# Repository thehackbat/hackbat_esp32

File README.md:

# HACKBAT ESP32 

New version of the Hackbat tool, this time based on the ESP32 C6. 

> NOTE: This version is still under test, so minor changes can be applied.

## The CPU

The new version of hackbat features a powerful [ESP32C6](https://www.espressif.com/en/products/socs/esp32-c6) from [Espressif](https://www.espressif.com). This microcontroller features a dual core RISC-V processor, WIFI6, BT LE and a bunch of peripherals. 

The package used is the WROOM-1, but it is also compatible with the 1U model adding an external antenna.

## RF

Like the original, the Hackbat ESP32 features an RF tranceiver, the [CC1101](https://www.ti.com/product/es-mx/CC1101) from Texas Instruments. 

The CC1101 is a low-cost sub-1 GHz transceiver designed for very low-power wireless applications. The circuit is mainly intended for the ISM (Industrial, Scientific and Medical) and SRD (Short Range Device) frequency bands at 315, 433, 868, and 915 MHz, but can easily be programmed for operation at other frequencies in the 300-348 MHz, 387-464 MHz and 779-928 MHz bands

The Hackbat ESP32 board includes an antenna, but can be also populate the J2 connector in order to add an SMA antenna.

## OLED

A monochrome OLED is added as an interface. The driver used in the ESP-IDF IDE is able to work with the SH1106, and ssd1306

## SDCard

The SD Card in this version uses the SDIO interface with the microcontroller, so the speed is increased with respect the first version of the board.

## Layout

The layout of the board is 2-layer with components in both layers.

## Get yours

This project is open-source so you can build your own Hackbat by sending the production files to [JLCPCB](https://jlcpcb.com/?from=controlpath).

[JLCPCB](https://jlcpcb.com/?from=controlpath) not only will manufacture your PCB, but they can also asembly your board. To do that, you have to use the BOM and the Centroid files provided in the [`production_files`](./kicad/production_files/) folder.

Remember to change the Surface Finish to LeadFree HASL to make your board ROHS compliant. Also, the original board uses a Black PCB color, so if you want to keep your Hackbat like the original, you can select this color to be sure that the silkscreen is seen correctly.

In a few days, you will receive your board at home.

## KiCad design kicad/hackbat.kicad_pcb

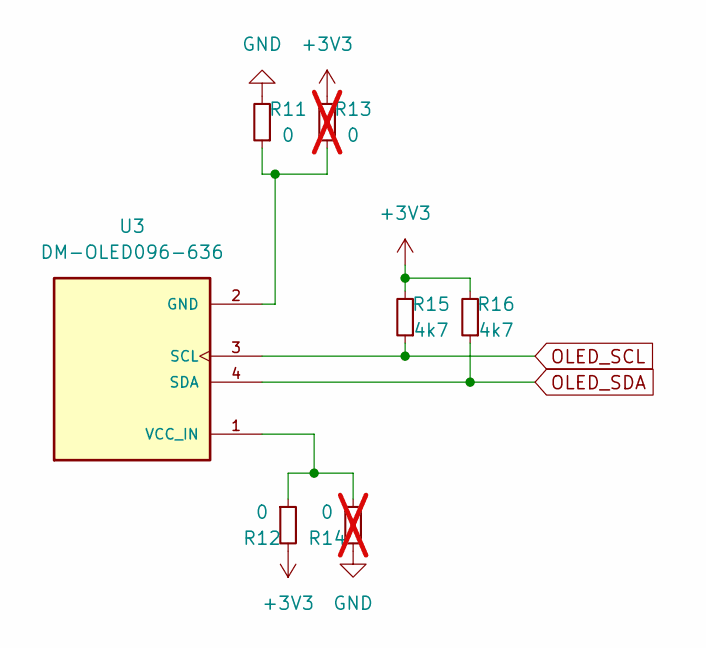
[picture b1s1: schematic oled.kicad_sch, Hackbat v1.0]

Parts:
R11, R12: 0; R_0603_1608Metric
R13, R14: 0; R_0603_1608Metric; not fitted
R15, R16: 4k7; R_0603_1608Metric
U3: DM-OLED096-636; oled_1.3; PARTREV 2018-09-10

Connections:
+3V3: R12.2, R13.2, R15.2, R16.2; also elsewhere on the board
GND: R11.2, R14.2; also elsewhere on the board
unnamed: R11.1, R13.1, U3.2 (GND)
unnamed: R12.1, R14.1, U3.1 (VCC_IN)
OLED_SCL: R15.1, U3.3 (SCL); also elsewhere on the board
OLED_SDA: R16.1, U3.4 (SDA); also elsewhere on the board

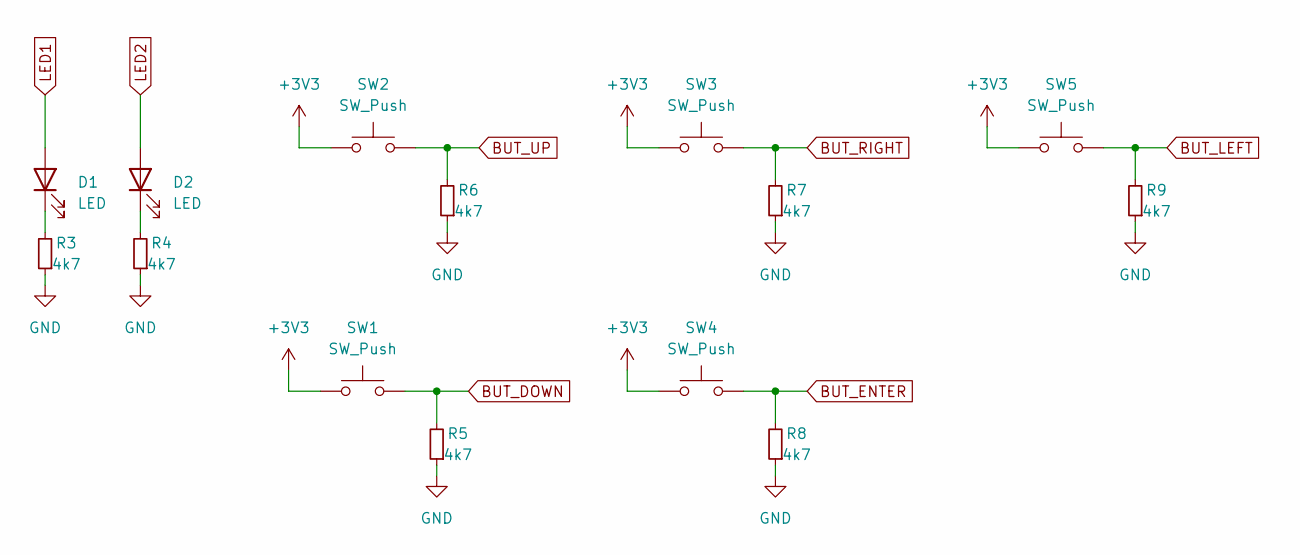
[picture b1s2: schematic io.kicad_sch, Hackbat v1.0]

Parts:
D1, D2: LED; LED_0603_1608Metric
R3, R4, R5, R6, R7, R8, R9: 4k7; R_0603_1608Metric
SW1, SW2, SW3, SW4, SW5: SW_Push; SW_Push_1P1T_NO_6x6mm_H9.5mm; JLCPCB Part # C455109

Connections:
+3V3: SW1.1, SW2.1, SW3.1, SW4.1, SW5.1; also elsewhere on the board
BUT_DOWN: R5.2, SW1.2; also elsewhere on the board
BUT_ENTER: R8.2, SW4.2; also elsewhere on the board
BUT_LEFT: R9.2, SW5.2; also elsewhere on the board
BUT_RIGHT: R7.2, SW3.2; also elsewhere on the board
BUT_UP: R6.2, SW2.2; also elsewhere on the board
GND: R3.1, R4.1, R5.1, R6.1, R7.1, R8.1, R9.1; also elsewhere on the board
LED1: D1.2 (A); also elsewhere on the board
LED2: D2.2 (A); also elsewhere on the board
unnamed: D1.1 (K), R3.2
unnamed: D2.1 (K), R4.2

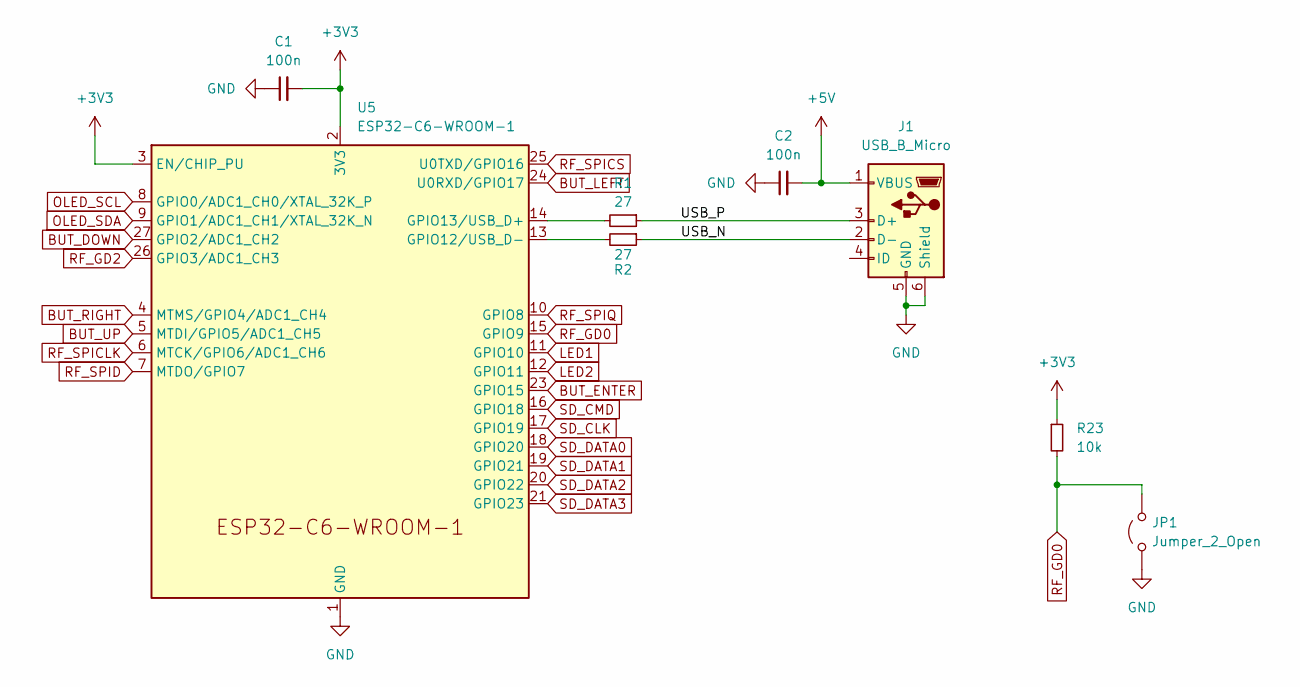
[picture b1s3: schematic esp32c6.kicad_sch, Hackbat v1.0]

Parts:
C1, C2: 100n; C_0603_1608Metric
J1: USB_B_Micro; USB_Micro-B_Amphenol_10118193-0001LF_Horizontal
JP1: Jumper_2_Open; TestPoint_2Pads_Pitch2.54mm_Drill0.8mm
R1, R2: 27; R_0603_1608Metric
R23: 10k; R_0402_1005Metric
U5: ESP32-C6-WROOM-1

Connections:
+3V3: C1.2, R23.1, U5.2 (3V3), U5.3 (EN/CHIP_PU); also elsewhere on the board
+5V: C2.2, J1.1 (VBUS); also elsewhere on the board
/esp32c6/USB_N: J1.2 (D-), R2.1
/esp32c6/USB_P: J1.3 (D+), R1.1
BUT_DOWN: U5.27 (GPIO2/ADC1_CH2); also elsewhere on the board
BUT_ENTER: U5.23 (GPIO15); also elsewhere on the board
BUT_LEFT: U5.24 (U0RXD/GPIO17); also elsewhere on the board
BUT_RIGHT: U5.4 (MTMS/GPIO4/ADC1_CH4); also elsewhere on the board
BUT_UP: U5.5 (MTDI/GPIO5/ADC1_CH5); also elsewhere on the board
GND: C1.1, C2.1, J1.5 (GND), J1.6 (Shield), JP1.1 (A), U5.1 (GND), U5.28 (GND), U5.29 (GND); also elsewhere on the board
LED1: U5.11 (GPIO10); also elsewhere on the board
LED2: U5.12 (GPIO11); also elsewhere on the board
unnamed: R2.2, U5.13 (GPIO12/USB_D-)
unnamed: R1.2, U5.14 (GPIO13/USB_D+)
OLED_SCL: U5.8 (GPIO0/ADC1_CH0/XTAL_32K_P); also elsewhere on the board
OLED_SDA: U5.9 (GPIO1/ADC1_CH1/XTAL_32K_N); also elsewhere on the board
RF_GD0: JP1.2 (B), R23.2, U5.15 (GPIO9); also elsewhere on the board
RF_GD2: U5.26 (GPIO3/ADC1_CH3); also elsewhere on the board
RF_SPICLK: U5.6 (MTCK/GPIO6/ADC1_CH6); also elsewhere on the board
RF_SPICS: U5.25 (U0TXD/GPIO16); also elsewhere on the board
RF_SPID: U5.7 (MTDO/GPIO7); also elsewhere on the board
RF_SPIQ: U5.10 (GPIO8); also elsewhere on the board
SD_CLK: U5.17 (GPIO19); also elsewhere on the board
SD_CMD: U5.16 (GPIO18); also elsewhere on the board
SD_DATA0: U5.18 (GPIO20); also elsewhere on the board
SD_DATA1: U5.19 (GPIO21); also elsewhere on the board
SD_DATA2: U5.20 (GPIO22); also elsewhere on the board
SD_DATA3: U5.21 (GPIO23); also elsewhere on the board

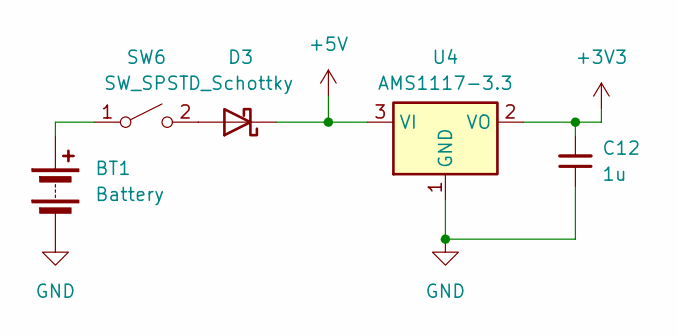
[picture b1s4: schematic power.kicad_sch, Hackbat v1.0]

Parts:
BT1: Battery; BatteryHolder_Keystone_2479_3xAAA
C12: 1u; C_0603_1608Metric
D3: D_Schottky; Nexperia_CFP3_SOD-123W; JLCPCB Part # C82544
SW6: SW_SPST; SW_SPDT_CK_JS102011SAQN; JLCPCB Part # C92658
U4: AMS1117-3.3; SOT-223-3_TabPin2

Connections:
+3V3: C12.2, U4.2 (VO); also elsewhere on the board
+5V: D3.1 (K), U4.3 (VI); also elsewhere on the board
GND: BT1.2 (-), C12.1, U4.1 (GND); also elsewhere on the board
unnamed: BT1.1 (+), SW6.1 (A)
unnamed: D3.2 (A), SW6.2 (B)

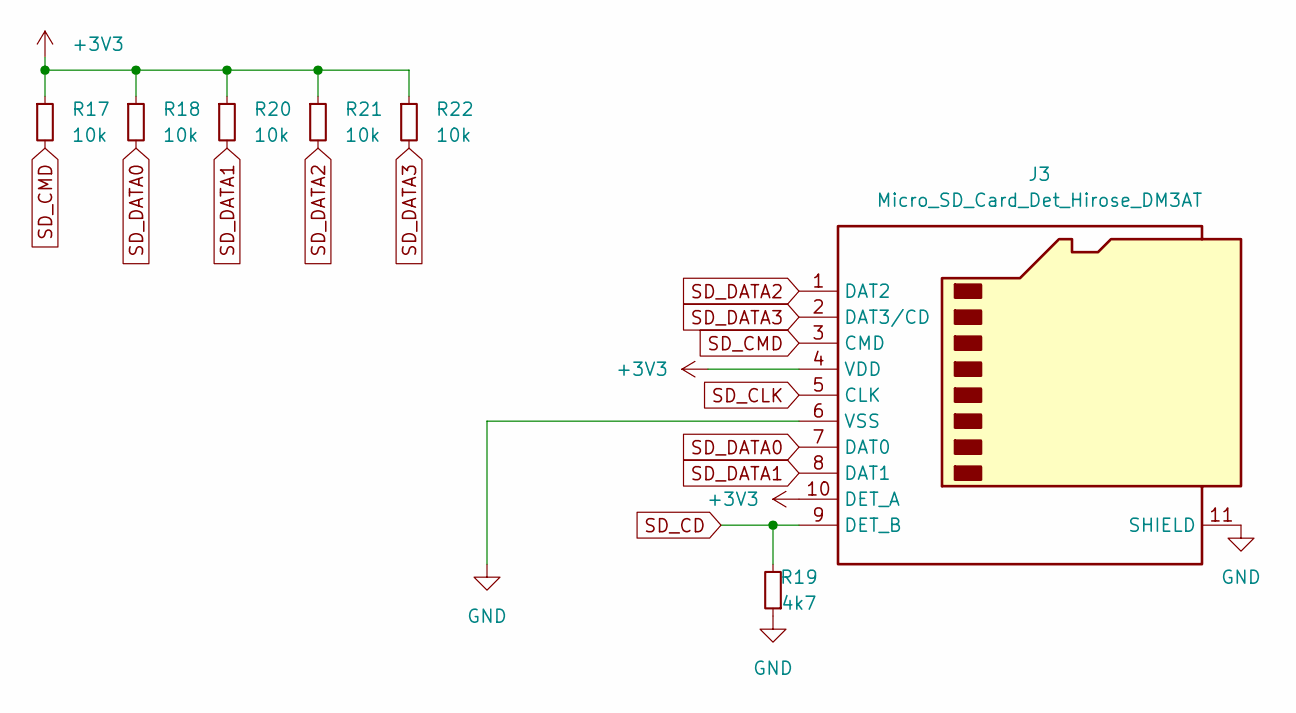
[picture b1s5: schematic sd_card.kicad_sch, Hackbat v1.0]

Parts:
J3: Micro_SD_Card_Det_Hirose_DM3AT; microSD_HC_Hirose_DM3AT-SF-PEJM5; JLCPCB Part # C114218
R17, R18, R20, R21, R22: 10k; R_0402_1005Metric
R19: 4k7; R_0603_1608Metric

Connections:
+3V3: J3.4 (VDD), J3.10 (DET_A), R17.1, R18.1, R20.1, R21.1, R22.1; also elsewhere on the board
GND: J3.6 (VSS), J3.11 (SHIELD), R19.1; also elsewhere on the board
SD_CD: J3.9 (DET_B), R19.2
SD_CLK: J3.5 (CLK); also elsewhere on the board
SD_CMD: J3.3 (CMD), R17.2; also elsewhere on the board
SD_DATA0: J3.7 (DAT0), R18.2; also elsewhere on the board
SD_DATA1: J3.8 (DAT1), R20.2; also elsewhere on the board
SD_DATA2: J3.1 (DAT2), R21.2; also elsewhere on the board
SD_DATA3: J3.2 (DAT3/CD), R22.2; also elsewhere on the board

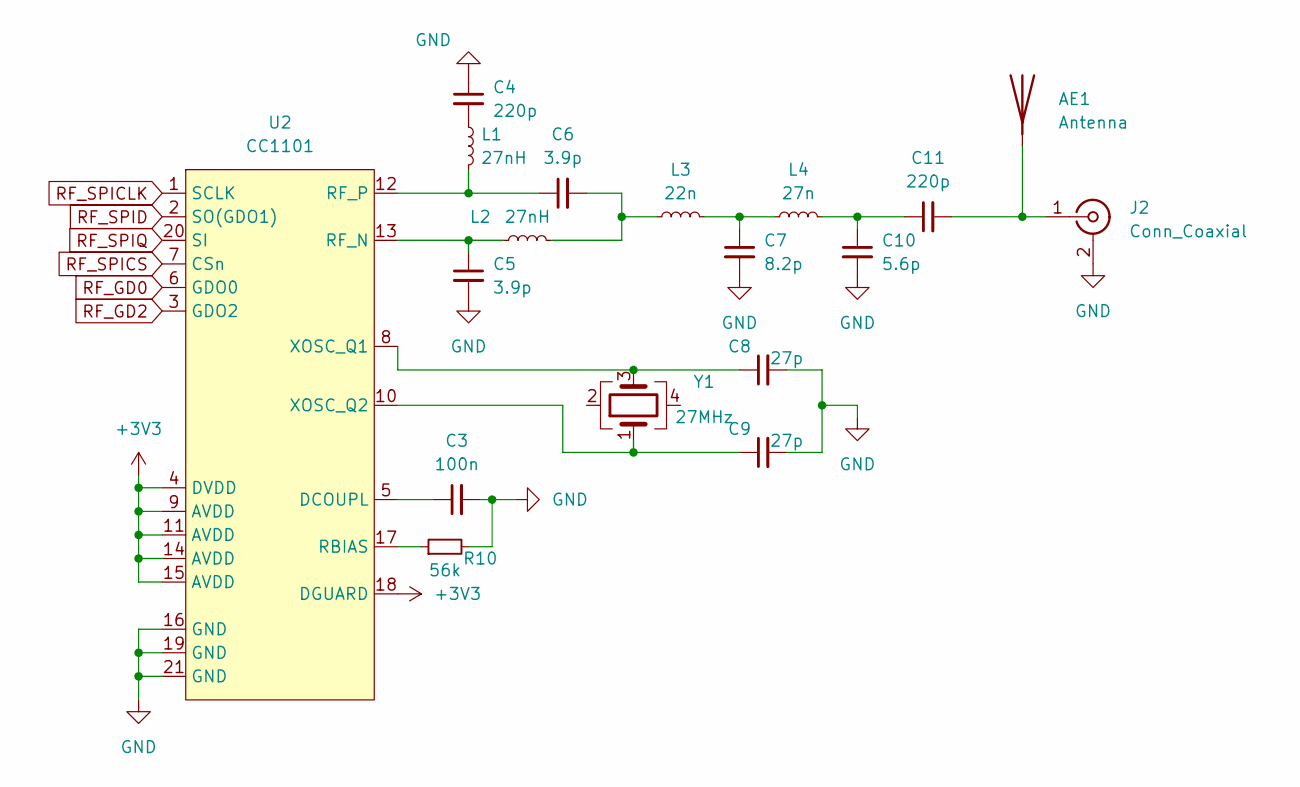
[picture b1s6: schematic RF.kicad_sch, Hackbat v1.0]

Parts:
AE1: Antenna; TestPoint_THTPad_1.5x1.5mm_Drill0.7mm
C3: 100n; C_0402_1005Metric
C4, C11: 220p; C_0402_1005Metric
C5, C6: 3.9p; C_0402_1005Metric
C7: 8.2p; C_0402_1005Metric
C8, C9: 27p; C_0402_1005Metric
C10: 5.6p; C_0402_1005Metric
J2: Conn_Coaxial; SMA_Amphenol_132289_EdgeMount
L1, L2: 27nH; L_0402_1005Metric
L3: 22n; L_0402_1005Metric
L4: 27n; L_0402_1005Metric
R10: 56k; R_0402_1005Metric
U2: CC1101; QFN-20-1EP_4x4mm_P0.5mm_EP2.6x2.6mm_ThermalVias; JLCPCB Part # C29953
Y1: 27MHz; Crystal_SMD_3225-4Pin_3.2x2.5mm; JLCPCB Part # C254353

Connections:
+3V3: U2.4 (DVDD), U2.9 (AVDD), U2.11 (AVDD), U2.14 (AVDD), U2.15 (AVDD), U2.18 (DGUARD); also elsewhere on the board
GND: C3.2, C4.1, C5.2, C7.2, C8.2, C9.2, C10.2, J2.2 (Ext), R10.2, U2.16 (GND), U2.19 (GND), U2.21 (GND); also elsewhere on the board
unnamed: AE1.1 (A), C11.2, J2.1 (In)
unnamed: C4.2, L1.1
unnamed: C6.2, L2.2, L3.1
unnamed: C7.1, L3.2, L4.1
unnamed: C10.1, C11.1, L4.2
unnamed: C3.1, U2.5 (DCOUPL)
unnamed: R10.1, U2.17 (RBIAS)
unnamed: C5.1, L2.1, U2.13 (RF_N)
unnamed: C6.1, L1.2, U2.12 (RF_P)
unnamed: C8.1, U2.8 (XOSC_Q1), Y1.3
unnamed: C9.1, U2.10 (XOSC_Q2), Y1.1
RF_GD0: U2.6 (GDO0); also elsewhere on the board
RF_GD2: U2.3 (GDO2); also elsewhere on the board
RF_SPICLK: U2.1 (SCLK); also elsewhere on the board
RF_SPICS: U2.7 (CSn); also elsewhere on the board
RF_SPID: U2.2 (SO(GDO1)); also elsewhere on the board
RF_SPIQ: U2.20 (SI); also elsewhere on the board

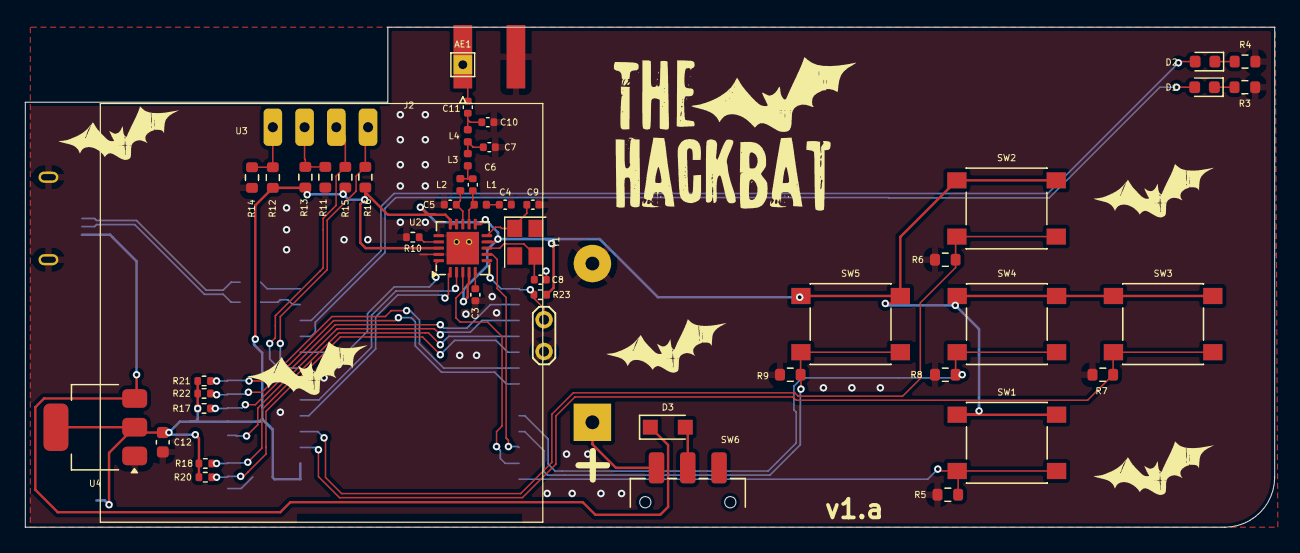
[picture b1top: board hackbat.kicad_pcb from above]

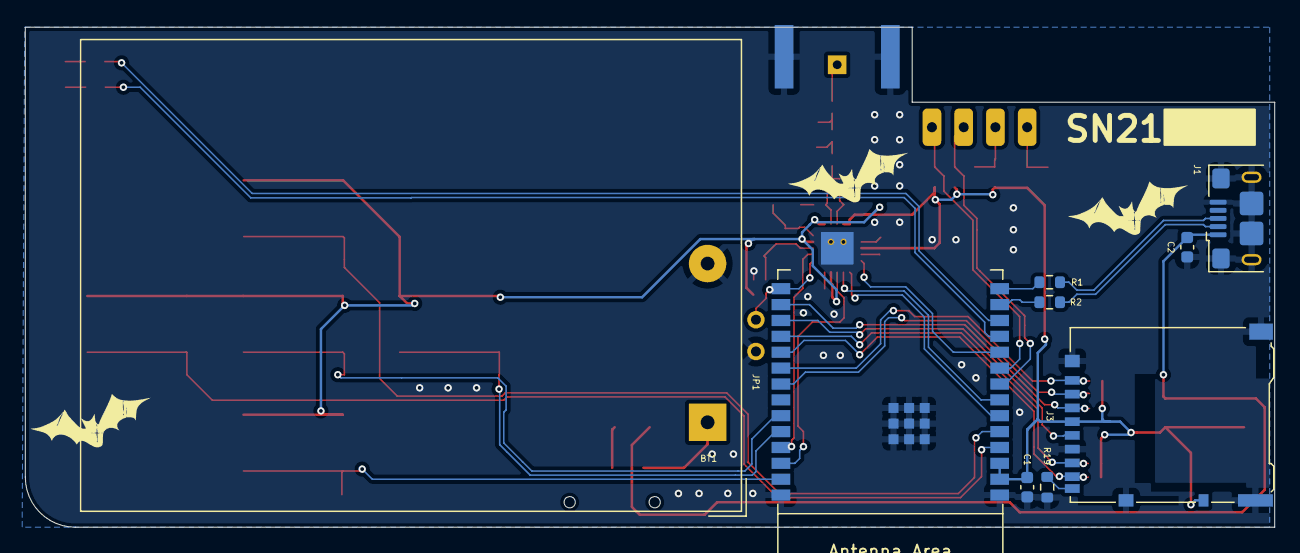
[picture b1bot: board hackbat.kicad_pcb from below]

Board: 2 copper layers, 99.9 x 40.0 mm, 59 parts (9 on the bottom side), 46 nets.

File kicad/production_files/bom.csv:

Reference,Value,Footprint,Qty,DNP,JLCPCB Part #
"C1,C2",100n,Capacitor_SMD:C_0603_1608Metric,2,,
C3,100n,Capacitor_SMD:C_0402_1005Metric,1,,
"C4,C11",220p,Capacitor_SMD:C_0402_1005Metric,2,,
"C5,C6",3.9p,Capacitor_SMD:C_0402_1005Metric,2,,
C7,8.2p,Capacitor_SMD:C_0402_1005Metric,1,,
"C8,C9",27p,Capacitor_SMD:C_0402_1005Metric,2,,
C10,5.6p,Capacitor_SMD:C_0402_1005Metric,1,,
C12,1u,Capacitor_SMD:C_0603_1608Metric,1,,
"D1,D2",LED,LED_SMD:LED_0603_1608Metric,2,,
D3,D_Schottky,Diode_SMD:Nexperia_CFP3_SOD-123W,1,,C82544
J1,USB_B_Micro,Connector_USB:USB_Micro-B_Amphenol_10118193-0001LF_Horizontal,1,,
J2,Conn_Coaxial,Connector_Coaxial:SMA_Amphenol_132289_EdgeMount,1,,
J3,Micro_SD_Card_Det_Hirose_DM3AT,Connector_Card:microSD_HC_Hirose_DM3AT-SF-PEJM5,1,,C114218
JP1,Jumper_2_Open,TestPoint:TestPoint_2Pads_Pitch2.54mm_Drill0.8mm,1,,
"L1,L2",27nH,Inductor_SMD:L_0402_1005Metric,2,,
L3,22n,Inductor_SMD:L_0402_1005Metric,1,,
L4,27n,Inductor_SMD:L_0402_1005Metric,1,,
"R1,R2",27,Resistor_SMD:R_0603_1608Metric,2,,
"R3,R4,R5,R6,R7,R8,R9,R15,R16,R19",4k7,Resistor_SMD:R_0603_1608Metric,10,,
R10,56k,Resistor_SMD:R_0402_1005Metric,1,,
"R11,R12",0,Resistor_SMD:R_0603_1608Metric,2,,
"R17,R18,R20,R21,R22,R23",10k,Resistor_SMD:R_0402_1005Metric,6,,
"SW1,SW2,SW3,SW4,SW5",SW_Push,Button_Switch_SMD:SW_Push_1P1T_NO_6x6mm_H9.5mm,5,,C455109
SW6,SW_SPST,Button_Switch_SMD:SW_SPDT_CK_JS102011SAQN,1,, C92658
U2,CC1101,Package_DFN_QFN:QFN-20-1EP_4x4mm_P0.5mm_EP2.6x2.6mm_ThermalVias,1,,C29953
U4,AMS1117-3.3,Package_TO_SOT_SMD:SOT-223-3_TabPin2,1,,
Y1,27MHz,Crystal:Crystal_SMD_3225-4Pin_3.2x2.5mm,1,,C254353

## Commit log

2024-12-22 added layout images
